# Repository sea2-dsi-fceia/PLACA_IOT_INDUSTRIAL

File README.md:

## Placa de desarrollo IoT Industrial basada en ESP32
## 📝 Descripción
Este repositorio contiene el diseño y la documentación de una placa de desarrollo robusta diseñada para aplicaciones de Internet de las Cosas Industrial (IIoT), domótica y enseñanza de sistemas embebidos. El corazón del sistema es un microcontrolador ESP32 de Espressif, integrado en un hardware capaz de soportar entornos industriales exigentes. 
La placa permite gestionar lógica programada para actuar sobre cargas de potencia (electroválvulas, motores, actuadores) bajo condiciones específicas de trabajo.

## 🚀 Características Técnicas
### Alimentación y Entradas
- **Voltaje de alimentación:** Soporta niveles industriales entre 12V y 24V CC.  
- **Entradas Digitales (4):** Optoaisladas para protección del microcontrolador, con soporte de niveles entre 5V y 24V y LEDs testigos.
**NOTA:** Las entradas digitales deben tener configuradas en el ESP32 las resistencias de PULL-DOWN internas o agregar de forma externa resistencias de PULL-DOWN para que las etapas de entrada funcionen de forma correcta.
- **Entradas Analógicas (2):** Rango de 0V a 10V con alta impedancia. 

### Salidas de Potencia 
- **Salidas a Relé (3):** Relés de simple inversor optoaislados, con capacidad de manejo en 220V CA o 24V CC.  
- **Salidas de Estado Sólido (5):** Implementadas con TRIACs optoaislados (MOC3021 y BT136) para cargas de 220V CA. 
- **Protección:** Diodos de freewheeling (1N4007) en antiparalelo con las bobinas de los relés para proteger los transistores driver.

### Periféricos e Interfaz
- **Pantalla OLED:** Comandada por protocolo $I^{2}C$ para interfaz HMI local.  
- **Almacenamiento:** Memoria EEPROM para datos no volátiles.  
- **Tiempo Real:** Reloj calendario (RTC) con batería de backup para registro de eventos.  Indicadores: LED RGB y alarma sonora (buzzer) para monitoreo de estados.

## 🛠️ Diseño de Hardware
El PCB fue diseñado en KiCad priorizando la robustez y la facilidad de mantenimiento:
- **Aislamiento Galvánico:** Uso de optoacopladores PC817 para separar la lógica de las etapas de potencia.  
- **Seguridad Eléctrica:** Muescas de aislación en la placa alrededor de los conectores comunes de los relés para evitar arcos de voltaje en 220V CA.
- **Dimensionamiento:** Pistas trazadas en ambas capas (TOP y BOTTOM) para mejorar el manejo de corriente y evitar sobrecalentamiento.

## 💻 Desarrollo de Software
La placa es versátil en cuanto a paradigmas de programación:
- **Sistemas Operativos en Tiempo Real (RTOS):** Soporte nativo para FreeRTOS y Zephyr, garantizando tiempos de respuesta determinísticos ante eventos críticos.
- **Estándar Industrial:** Compatible con el proyecto OpenPLC, permitiendo programación en lenguaje Ladder bajo la norma IEC 61131-3.
- **Conectividad IIoT:** Implementación de protocolos como Modbus TCP, MQTT para telemetría, WebSockets y Webservers embebidos con interfaces HTML.  

## 📂 Ejemplo de Aplicación: Control de Caldera
El proyecto incluye un ejemplo integrador de un sistema de control de temperatura con seguridad por presión: 
- **Sensor:** Lectura de temperatura vía LM35 en entrada analógica.  
- **Seguridad:** Detección de alta presión mediante sensor digital que desactiva el calefactor y activa un ventilador de emergencia.  
- **Telemetría:** Monitoreo remoto mediante una webapp alojada en el propio microcontrolador.

## 📈 Roadmap y Mejoras Futuras
- Integración de puerto Ethernet nativo.  
- Implementación de buses de campo: RS-485 y CAN BUS.  
- Fuente de alimentación conmutada tipo Buck DC-DC para mayor eficiencia

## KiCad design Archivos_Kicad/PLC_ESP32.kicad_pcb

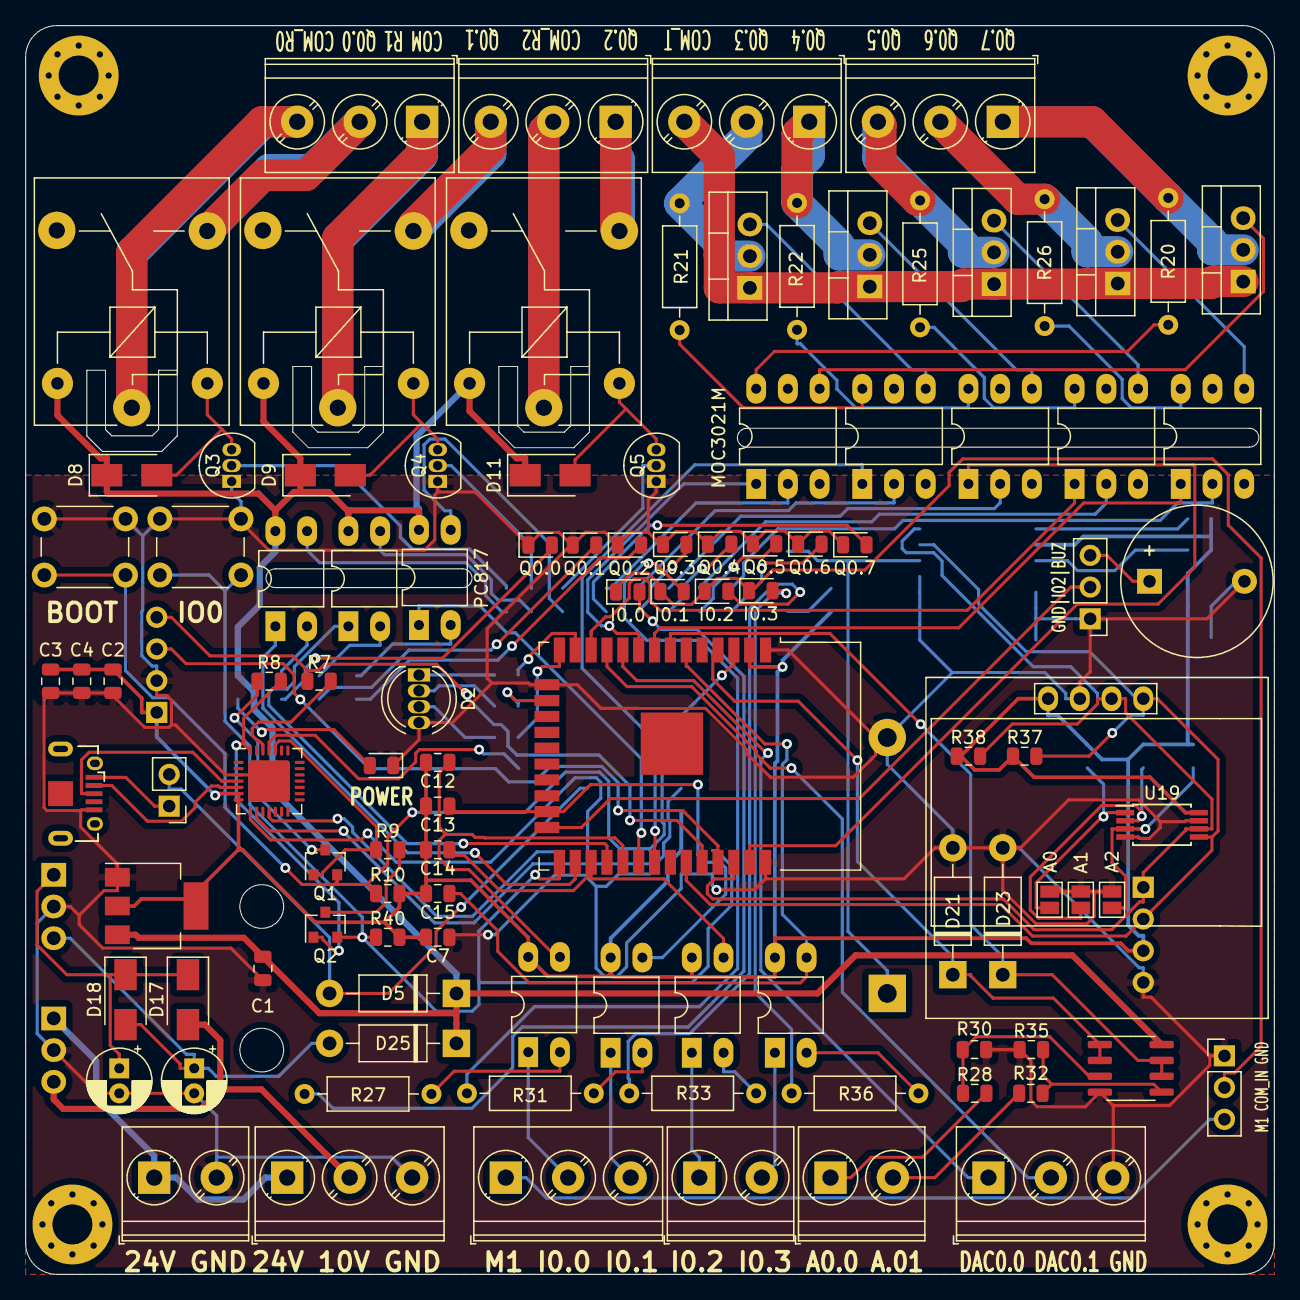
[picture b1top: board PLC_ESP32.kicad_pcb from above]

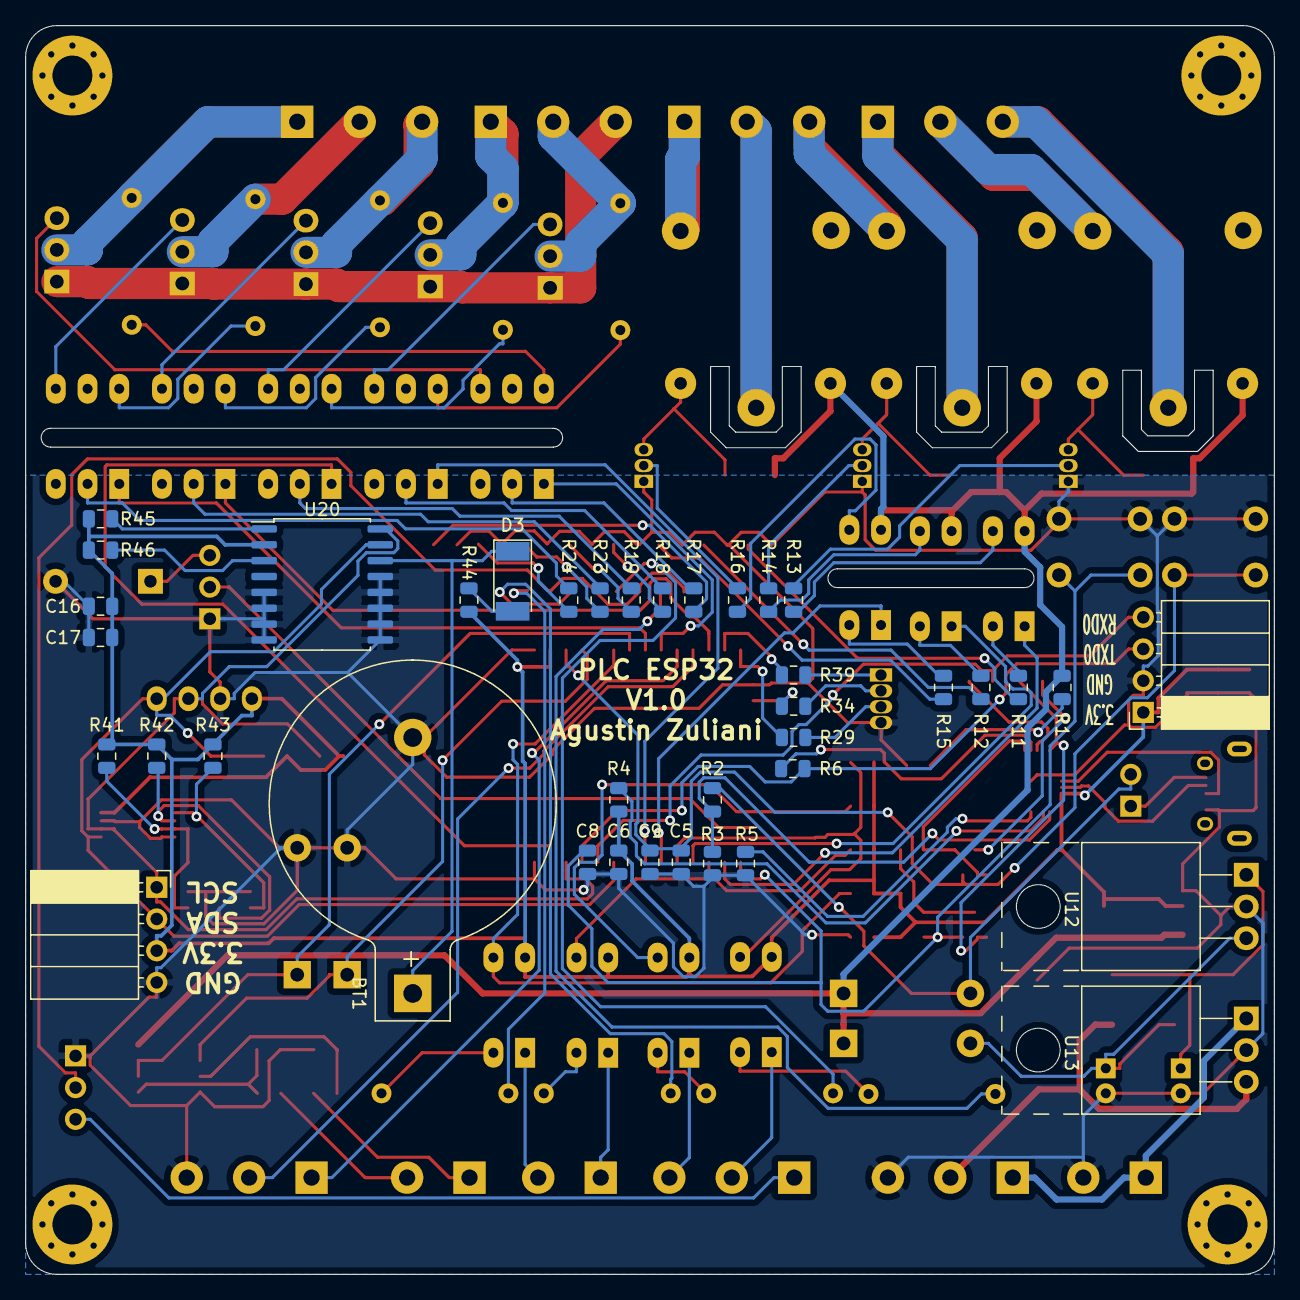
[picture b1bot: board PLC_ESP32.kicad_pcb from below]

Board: 2 copper layers, 100.0 x 100.0 mm, 148 parts (39 on the bottom side), 123 nets.

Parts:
A0, A1, A2: Jumper; SolderJumper-2_P1.3mm_Open_Pad1.0x1.5mm
BT1: Battery_Cell; BatteryHolder_Keystone_103_1x20mm
BZ1: Buzzer; Buzzer_12x9.5RM7.6
C1, C4, C6: 22uF/10V(20%); C_0805_2012Metric
C2: 47uf/6.3V(10%); C_0805_2012Metric
C3, C5, C7, C8, C9: 0.1uf/50V(10%); C_0805_2012Metric
C10: 0.33uf; CP_Radial_D5.0mm_P2.00mm
C11: 0.1uf; CP_Radial_D5.0mm_P2.00mm
C12, C13, C14, C15: 100nf; C_0805_2012Metric
C16, C17: 0.1uf; C_0805_2012Metric
D1: LED RED; LED_0805_2012Metric
D2: LED_RGBC; LED_D5.0mm-4_RGB
D3: 1N4148; D_MELF
D5, D25: BAT760-7 30V 1A; D_DO-41_SOD81_P10.16mm_Horizontal
D6: Q0.0; LED_0805_2012Metric
D7: Q0.1; LED_0805_2012Metric
D8, D9, D11, D17, D18: 1N4007; D_SMA
D10: Q0.2; LED_0805_2012Metric
D12: Q0.7; LED_0805_2012Metric
D13: Q0.3; LED_0805_2012Metric
D14: Q0.4; LED_0805_2012Metric
D15: Q0.5; LED_0805_2012Metric
D16: Q0.6; LED_0805_2012Metric
D19: I0.0; LED_0805_2012Metric
D20: I0.1; LED_0805_2012Metric
D21, D23: 1N4728A/3.3V; D_DO-41_SOD81_P10.16mm_Horizontal
D22: I0.2; LED_0805_2012Metric
D24: I0.3; LED_0805_2012Metric
J1: USB_B_Micro; Conn_USBmicro-B_ebay-side_TH
J2, J3: Terminales Reles; TerminalBlock_Phoenix_PT-1,5-3-5.0-H_1x03_P5.00mm_Horizontal
J4, J5: Terminales Triacs; TerminalBlock_Phoenix_PT-1,5-3-5.0-H_1x03_P5.00mm_Horizontal
J6: Entrada_24VDC; TerminalBlock_Phoenix_PT-1,5-2-5.0-H_1x02_P5.00mm_Horizontal
J7: PANTALLA LCD I2C; PinSocket_1x04_P2.54mm_Horizontal
J9: PANTALLA OLED; 128x64OLED
J10: Salidas Analogicas; TerminalBlock_Phoenix_PT-1,5-3-5.0-H_1x03_P5.00mm_Horizontal
J12: UART_SERIE; PinSocket_1x04_P2.54mm_Horizontal
J13, J14: Entrada Digital; TerminalBlock_Phoenix_PT-1,5-3-5.0-H_1x03_P5.00mm_Horizontal
J15: Entrada Digital; TerminalBlock_Phoenix_PT-1,5-2-5.0-H_1x02_P5.00mm_Horizontal
J16: Entrada Analogica; TerminalBlock_Phoenix_PT-1,5-2-5.0-H_1x02_P5.00mm_Horizontal
JP1: Habilitacion VBUS; PinHeader_1x02_P2.54mm_Vertical
JP2: Comun Entradas; PinHeader_1x03_P2.54mm_Vertical
JP3: IO2; PinHeader_1x03_P2.54mm_Vertical
K1, K2, K3: SANYOU_SRD_Form_C; Relay_SPDT_SANYOU_SRD_Series_Form_C
Q1, Q2: SS8050-G; SOT-23
Q3, Q4, Q5: 2N2219; TO-92_Inline
Q6, Q7, Q8, Q9, Q10: BT136-500; TO-220-3_Vertical
R1, R4: 2K(5%); R_0805_2012Metric
R2: 22.1K(5%); R_0805_2012Metric
R3: 47.5K(5%); R_0805_2012Metric
R5, R8, R9, R10, R40: 10K(5%); R_0805_2012Metric
R6, R7: 0R(5%); R_0805_2012Metric
R11, R12, R15, R17, R18, R19, R23, R24: 45/ 1/8W (5%); R_0805_2012Metric
R13, R14, R16: 2K; R_0805_2012Metric
R20, R21, R22, R25, R26: 33K; R_Axial_DIN0207_L6.3mm_D2.5mm_P10.16mm_Horizontal
R27, R31, R33, R36: 1K/0.5W (5%); R_Axial_DIN0207_L6.3mm_D2.5mm_P10.16mm_Horizontal
R28, R32: 1K/ 1/8W (5%); R_0805_2012Metric
R29, R34, R39: 100 Ohm 1/8W 5%; R_0805_2012Metric
R30, R35: 2K/ 1/8W (5%); R_0805_2012Metric
R37, R38: 2K2 (5%); R_0805_2012Metric
R41, R42, R43, R45, R46: 4K7 1/8W 5%; R_0805_2012Metric
R44: 200 1/8W 5%; R_0805_2012Metric
REF1, REF1#2, REF1#3, REF1#4: MountingHole_3.2mm_M3_Pad_Via
SW1, SW2: SW_Push; SW_PUSH_6mm
U1: AMS1117-3.3; SOT-223-3_TabPin2
U2: CP2102N-A01-GQFN28; QFN-28-1EP_5x5mm_P0.5mm_EP3.35x3.35mm
U3: ESP32-WROOM-32
U4, U5, U6, U14, U16, U17, U18: PC817; DIP-4_W7.62mm_LongPads
U7, U8, U9, U10, U11: MOC3021M; DIP-6_W7.62mm_LongPads
U12: LM7805_TO220; TO-220-3_Horizontal_TabUp
U13: LM7810_TO220; TO-220-3_Horizontal_TabUp
U15: LM358; SOIC-8_3.9x4.9mm_P1.27mm
U19: AT24CS32-XHM; TSSOP-8_4.4x3mm_P0.65mm
U20: DS3231M; SOIC-16W_7.5x10.3mm_P1.27mm

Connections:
+3V3: C2.2, C3.2, C4.1, C6.2, C7.2, C12.1, C13.1, C14.1, C15.1, C16.1, C17.1, J7.3, J9.1, J12.1, R4.2, R10.1, R37.1, R38.1, R40.2, R41.1, R42.1, R43.1, R44.2, R45.1, R46.1, U1.2, U2.6, U2.7, U3.2, U14.4, U16.4, U17.4, U18.4, U19.8, U20.2
+5V: C1.1, D5.1, D8.1, D9.1, D11.1, D25.1, K1.5, K2.5, K3.5, R1.1, U1.3, U4.4, U5.4, U6.4, U15.8
+10V: D17.2, J13.2, U13.3
+24V: J6.1, J13.1, U13.1
/Control/A0.0: D21.1, U3.4, U15.1, U15.2
/Control/A0.1: D23.1, U3.7, U15.6, U15.7
/Control/ACTIVE: R5.1, U2.11
/Control/D+: J1.3, U2.4
/Control/D-: J1.2, U2.5
/Control/DAC0.0: J10.1, U3.10
/Control/DAC0.1: J10.2, U3.11
/Control/DTR: Q2.1, R8.2, U2.28
/Control/EN: C5.1, C9.1, Q1.2, R10.2, SW2.2, U3.3
/Control/I0.0: C12.2, U3.29, U14.3
/Control/I0.1: C13.2, U3.23, U16.3
/Control/I0.2: C14.2, U3.27, U17.3
/Control/I0.3: C15.2, U3.6, U18.3
/Control/IO0: C8.1, Q2.2, R40.1, SW1.2, U3.25
/Control/IO2: JP3.2, U3.24
/Control/IO12: R29.2, U3.14
/Control/IO13: R34.2, U3.16
/Control/IO14: R39.2, U3.13
/Control/Q0.0: U3.26, U4.1
/Control/Q0.1: U3.28, U5.1
/Control/Q0.2: U3.30, U6.1
/Control/Q0.3: U3.31, U8.1
/Control/Q0.4: U3.37, U9.1
/Control/Q0.5: U3.12, U10.1
/Control/Q0.6: U3.8, U11.1
/Control/Q0.7: U3.9, U7.1
/Control/RTS: Q1.1, R9.2, U2.24
/Control/RXD: R6.2, U2.25
/Control/RXD0: J12.4, R7.1, U3.34
/Control/SCL: J7.1, J9.3, R38.2, U3.36, U19.6, U20.16
/Control/SDA: J7.2, J9.4, R37.2, U3.33, U19.5, U20.15
/Control/TXD: R7.2, U2.26
/Control/TXD0: J12.3, R6.1, U3.35
/Entradas/AN0.0: J16.1, R28.1
/Entradas/AN0.1: J16.2, R32.1
/Entradas/COM_IN: D19.1, D20.1, D22.1, D24.1, JP2.2
/Entradas/In0.0: J14.2, U14.1
/Entradas/In0.1: J14.3, U16.1
/Entradas/In0.2: J15.1, U17.1
/Entradas/In0.3: J15.2, U18.1
/Entradas/M1: J14.1, JP2.3
/Salidas/COM_RELE1: J2.3, K1.1
/Salidas/COM_RELE2: J2.1, K2.1
/Salidas/COM_RELE3: J3.2, K3.1
/Salidas/COM_TRIAC: J4.3, Q6.1, Q7.1, Q8.1, Q9.1, Q10.1
/Salidas/Q0.0_NA: J2.2, K1.3
/Salidas/Q0.1_NA: J3.3, K2.3
/Salidas/Q0.2_NA: J3.1, K3.3
/Salidas/Q0.3_NA: J4.2, Q7.2, R21.1
/Salidas/Q0.4_NA: J4.1, Q8.2, R22.1
/Salidas/Q0.5_NA: J5.3, Q9.2, R25.1
/Salidas/Q0.6_NA: J5.2, Q10.2, R26.1
/Salidas/Q0.7_NA: J5.1, Q6.2, R20.1
GND: A0.1, A1.1, A2.1, BT1.2, BZ1.2, C1.2, C2.1, C3.1, C4.2, C5.2, C6.1, C7.1, C8.2, C9.2, C10.2, C11.2, C16.2, C17.2, D1.1, D2.4, D6.1, D7.1, D10.1, D12.1, D13.1, D14.1, D15.1, D16.1, D21.2, D23.2, J1.5, J6.2, J7.4, J9.2, J10.3, J12.2, J13.3, JP2.1, JP3.1, Q3.1, Q4.1, Q5.1, R3.1, R5.2, R30.2, R35.2, SW1.1, SW2.1, U1.1, U2.3, U2.29, U3.1, U3.15, U3.38, U12.2, U13.2, U15.4, U19.4, U19.7, U20.5, U20.6, U20.7, U20.8, U20.9, U20.10, U20.11, U20.12, U20.13
unnamed: A0.2, R43.2, U19.1
unnamed: A1.2, R42.2, U19.2
unnamed: A2.2, R41.2, U19.3
unnamed: BT1.1, D3.1, U20.14
unnamed: BZ1.1, JP3.3
unnamed: C10.1, D17.1, D18.1, U12.1
unnamed: C11.1, D18.2, D25.2, U12.3
unnamed: D1.2, R1.2
unnamed: D2.1, R39.1
unnamed: D2.2, R34.1
unnamed: D2.3, R29.1
unnamed: D3.2, R44.1
unnamed: D6.2, R11.2
unnamed: D7.2, R12.2
unnamed: D8.2, K1.2, Q3.3
unnamed: D9.2, K2.2, Q4.3
unnamed: D10.2, R15.2
unnamed: D11.2, K3.2, Q5.3
unnamed: D12.2, R17.2
unnamed: D13.2, R18.2
unnamed: D14.2, R19.2
unnamed: D15.2, R23.2
unnamed: D16.2, R24.2
unnamed: D19.2, R27.2
unnamed: D20.2, R31.2
unnamed: D22.2, R33.2
unnamed: D24.2, R36.2
unnamed: J1.1, JP1.1
unnamed: Q1.3, R8.1
unnamed: Q2.3, R9.1
unnamed: Q3.2, R13.2
unnamed: Q4.2, R14.2
unnamed: Q5.2, R16.2
unnamed: Q6.3, U7.4
unnamed: Q7.3, U8.4
unnamed: Q8.3, U9.4
unnamed: Q9.3, U10.4
unnamed: Q10.3, U11.4
unnamed: R2.1, R3.2, U2.8
unnamed: R4.1, U2.9
unnamed: R11.1, U4.2
unnamed: R12.1, U5.2
unnamed: R13.1, U4.3
unnamed: R14.1, U5.3
unnamed: R15.1, U6.2
unnamed: R16.1, U6.3
unnamed: R17.1, U7.2
unnamed: R18.1, U8.2
unnamed: R19.1, U9.2
unnamed: R20.2, U7.6
unnamed: R21.2, U8.6
unnamed: R22.2, U9.6
unnamed: R23.1, U10.2
unnamed: R24.1, U11.2
unnamed: R25.2, U10.6
unnamed: R26.2, U11.6
unnamed: R27.1, U14.2
unnamed: R28.2, R30.1, U15.3
unnamed: R31.1, U16.2
unnamed: R32.2, R35.1, U15.5
unnamed: R33.1, U17.2
unnamed: R36.1, U18.2
unnamed: R45.2, U20.1
unnamed: R46.2, U20.3
VBUS: D5.2, JP1.2, R2.2

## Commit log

2026-05-14 Update README title for clarity
2026-05-14 Change header level in README.md
2026-05-14 Refactor section headings in README.md
    Updated section headings in README.md for better visibility and consistency.
